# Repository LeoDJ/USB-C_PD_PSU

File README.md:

# USB-C PD PSU
> [!WARNING]
> This is a WIP project. It is not yet recommended to reproduce it in its current state. 

A bidirectional buck-boost DC-DC converter with the following features:
- 240W USB PD EPR (48V 5A)*
- 5-60V input
- 3.3-60V output
- 20A maximum current (theoretically, depending on the thermal solution)
- Constant-current control
- `TI BQ25758A` DC-DC controller
- `WCH CH32X035` as the USB Type-C PD controller (hopefully*)
- Protection of CC and USB data lines up to 63V (`TI TPD4S480`)
- Rough mechanical compatibility with [FranzImsch's parkside-adapter](https://github.com/FranzImsch/parkside-adapter)
- A separate-ish "HMI"/"UI" part of the PCB containing:
  - `XT30` connectors for power in/output
  - 1.47" IPS display
  - Encoder + button controls
  - 1.27mm 2x06 expansion header with a few GPIOs / RS485 for potentially communicating with BMS's, etc.
  - A second `CH32X035`
  - Separable via rotary cutting tool (no mouse bites, because of the high current connections to the XT30 plugs and to not fall into the JLCPCB "two designs" price tier)
- 50x50mm PCB size (50x23mm without the "UI" part)

\* depending on the yet-to-be-written PD firmware (and an actually functioning DC-DC converter layout :P)

You can follow the [Mastodon thread](https://chaos.social/@LeoDJ/113874922536756547) for more up-to-date progress on this project.

&nbsp;

## Hardware
The v1.0 PCB is designed in 8 layers, but 6 would probably suffice too. Thus inner layers 3 and 4 were designed as containing only more GND / power copper pours and can probably be left out, only leading to a reduction of a combined copper thickness from 175µm to 140µm.

### JLCPCB Ordering Settings
- Default, except:
- PCB Thickness: `1.0mm`
- Mark on PCB: `Remove Mark`
- Stencil:
  - (Stencil Side: `Top`)
  - Customized Size: `Yes - 200 x 200mm` (saves on shipping cost)

## References
- ESD-Paw symbol: [diminDDL](https://github.com/diminDDL) ([Source](https://github.com/Caraffa-git/PCB-Art/tree/main/SVG/ESD-paw))
- Paw-shaped Tag-Connect pawprint: [Paw-Connect](https://github.com/LeoDJ/Paw-Connect)

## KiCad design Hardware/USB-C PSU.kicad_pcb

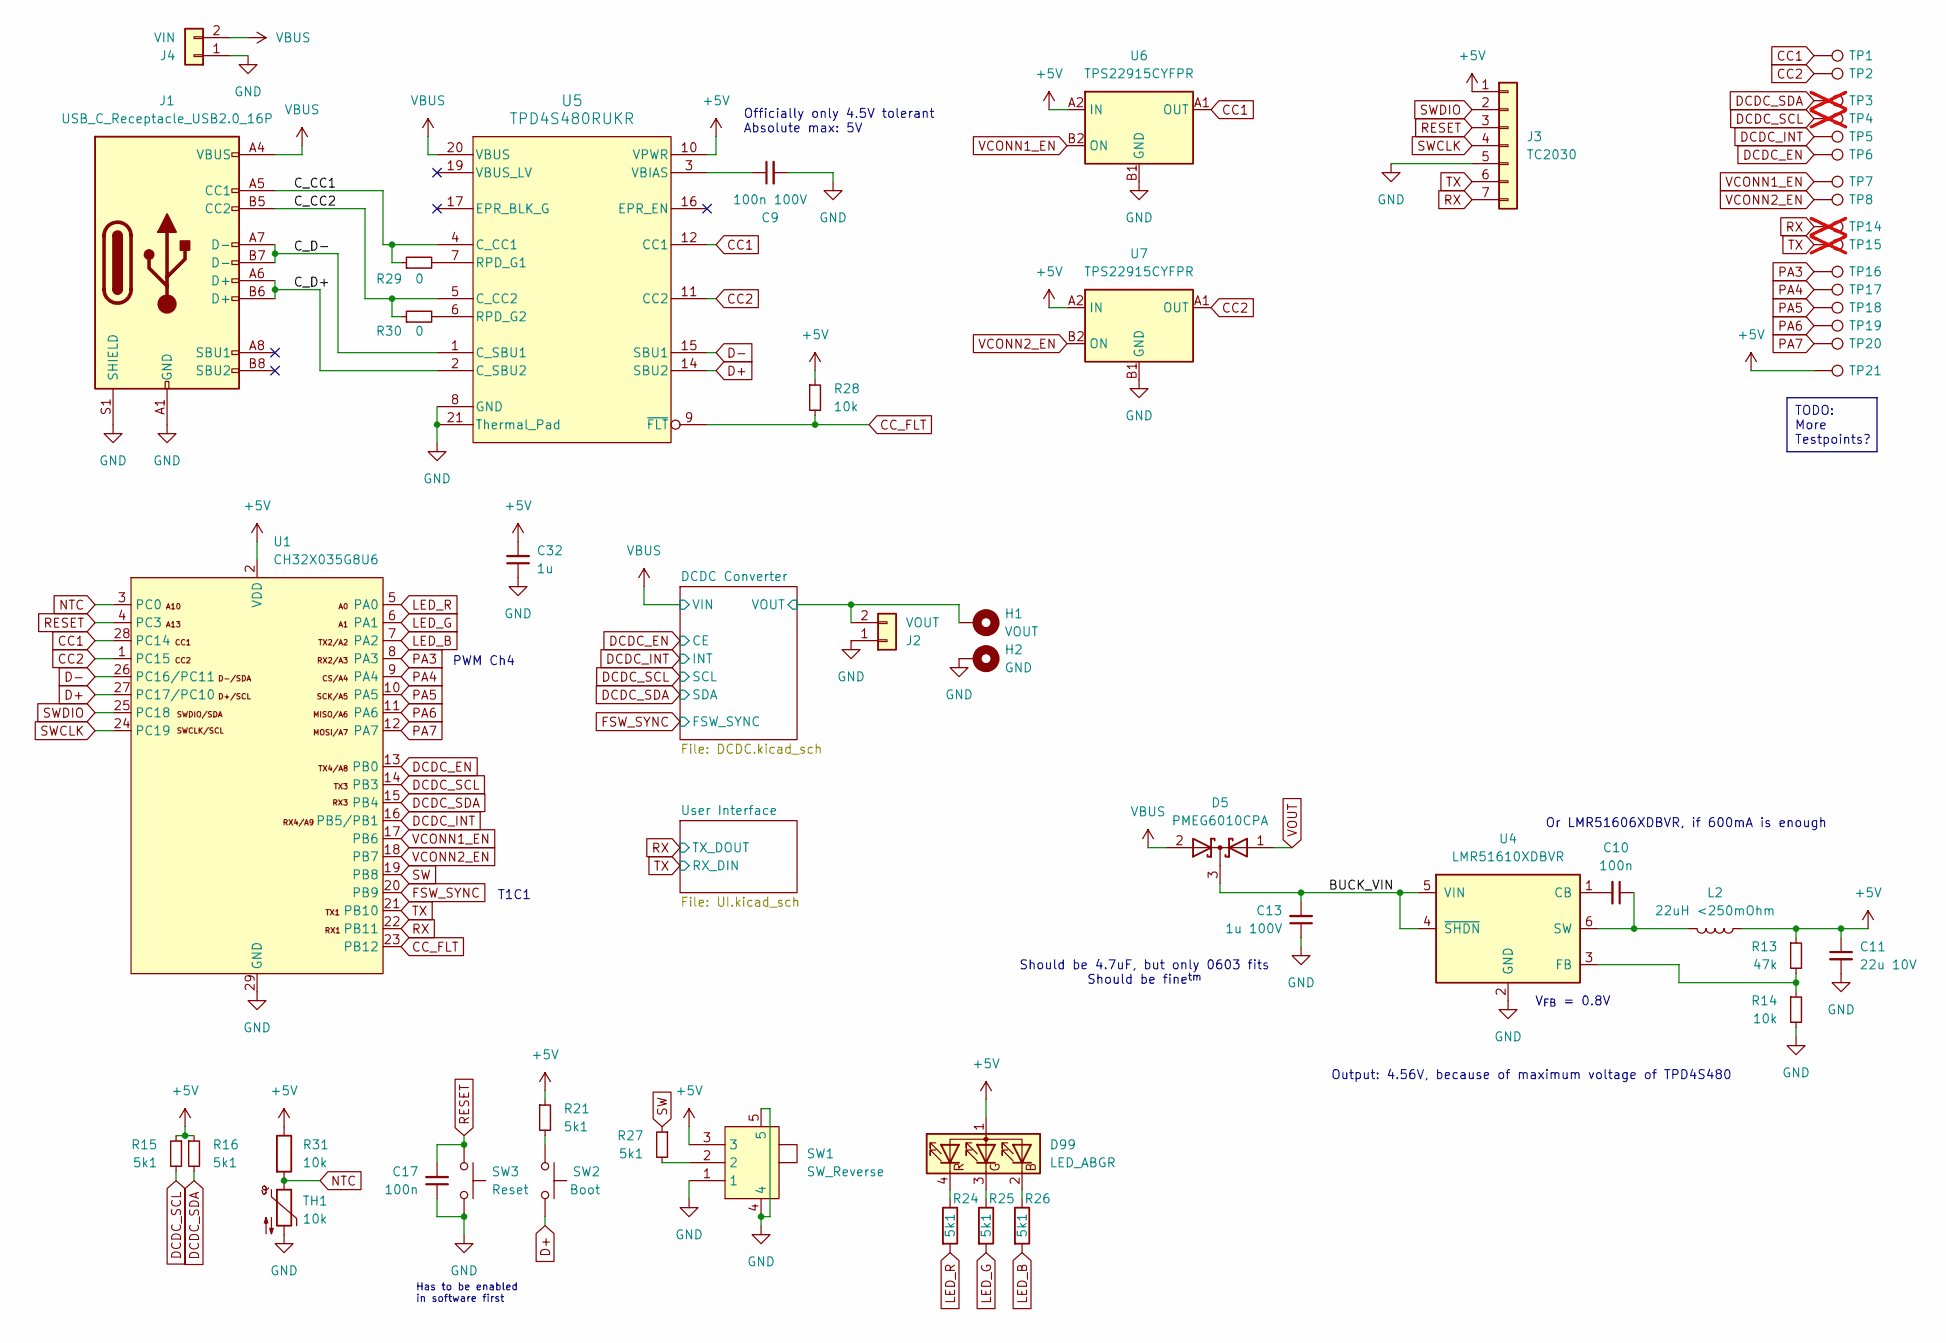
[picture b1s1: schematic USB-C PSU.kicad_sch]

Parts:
C9: 100n 100V; C_0402_1005Metric
C10, C17: 100n; C_0402_1005Metric
C11: 22u 10V; C_0603_1608Metric; LCSC Part C86295
C13: 1u 100V; C_0603_1608Metric
C32: 1u; C_0402_1005Metric
D5: PMEG6010CPA; HUSON-3-1EP_2x2mm_P1.3mm_EP1.1x1.6mm
D99: LED_ABGR; LED-ARRAY-SMD_MHS110FRGBCT; LCSC Part C389528
H1: VOUT; MountingHole_2.2mm_M2_Pad_Via
H2: GND; MountingHole_2.2mm_M2_Pad_Via
J1: USB_C_Receptacle_USB2.0_16P; USB_C_Receptacle_HRO_TYPE-C-31-M-12
J2: VOUT; AMASS_XT30PW-M_1x02_P2.50mm_Horizontal; LCSC Part C431092
J3: TC2030; Paw-Connect_RevB_TC2030-IDC-NL_2x03_P1.27mm_Vertical
J4: VIN; AMASS_XT30PW-M_1x02_P2.50mm_Horizontal; LCSC Part C431092
L2: 22uH <250mOhm; L_Sunlord_MWSA0503S; LCSC Part C718383
R13: 47k; R_0402_1005Metric
R14, R28, R31: 10k; R_0402_1005Metric
R15, R16, R21, R24, R25, R26, R27: 5k1; R_0402_1005Metric
R29, R30: 0; R_0402_1005Metric
SW1: SW_Reverse; SW-SMD_MSK12CO2; LCSC Part C2681570
SW2: Boot; SW-SMD_4P-L3.0-W2.0-P0.85-LS3.5; LCSC Part C256107
SW3: Reset; SW-SMD_4P-L3.0-W2.0-P0.85-LS3.5; LCSC Part C256107
TH1: 10k; R_0402_1005Metric; LCSC Part C77131
TP1, TP2, TP5, TP6, TP7, TP8, TP16, TP17, TP18, TP19, TP20, TP21: TestPoint; TestPoint_Pad_D1.0mm
TP3, TP4, TP14, TP15: TestPoint; TestPoint_Pad_D1.0mm; not fitted
U1: CH32X035G8U6; QFN-28-1EP_4x4mm_P0.4mm_EP2.6x2.6mm; LCSC Part C7437027
U4: LMR51610XDBVR; SOT-23-6; LCSC Part C20539658
U5: TPD4S480RUKR; WQFN-20-1EP_3x3mm_P0.4mm_EP1.7x1.7mm
U6, U7: TPS22915CYFPR; Texas_PicoStar_BGA-4_0.758x0.758mm_Layout2x2_P0.4mm; LCSC Part C1849498

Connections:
+5V: C11.1, C32.2, D99.1 (A), J3.1, L2.2, R13.1, R15.1, R16.1, R21.1, R28.1, R31.1, SW1.3, TP21.1, U1.2 (VDD), U5.10 (VPWR), U6.A2 (IN), U7.A2 (IN); also elsewhere on the board
/BUCK_VIN: C13.2, D5.3 (K), U4.4 (~SHDN), U4.5 (VIN)
/C_CC1: J1.A5 (CC1), R29.1, U5.4 (C_CC1)
/C_CC2: J1.B5 (CC2), R30.1, U5.5 (C_CC2)
/C_D+: J1.A6 (D+), J1.B6 (D+), U5.2 (C_SBU2)
/C_D-: J1.A7 (D-), J1.B7 (D-), U5.1 (C_SBU1)
CC1: TP1.1, U1.28 (PC14), U5.12 (CC1), U6.A1 (OUT)
CC2: TP2.1, U1.1 (PC15), U5.11 (CC2), U7.A1 (OUT)
CC_FLT: R28.2, U1.23 (PB12), U5.9 (~FLT)
D+: SW2.1, U1.27 (PC17/PC10), U5.14 (SBU2)
D-: U1.26 (PC16/PC11), U5.15 (SBU1)
DCDC_EN: TP6.1, U1.13 (PB0); also elsewhere on the board
DCDC_INT: TP5.1, U1.16 (PB5/PB1); also elsewhere on the board
DCDC_SCL: R15.2, TP4.1, U1.14 (PB3); also elsewhere on the board
DCDC_SDA: R16.2, TP3.1, U1.15 (PB4); also elsewhere on the board
FSW_SYNC: U1.20 (PB9); also elsewhere on the board
GND: C9.2, C11.2, C13.1, C17.1, C32.1, H2.1, J1.A1 (GND), J1.A12 (GND), J1.B1 (GND), J1.B12 (GND), J1.S1 (SHIELD), J2.1, J3.5, J4.1, R14.2, SW1.1, SW1.4, SW1.5, SW3.2, TH1.2, U1.29 (GND), U4.2 (GND), U5.8 (GND), U5.13 (GND), U5.18 (GND), U5.21 (Thermal_Pad), U6.B1 (GND), U7.B1 (GND); also elsewhere on the board
LED_B: R26.2, U1.7 (PA2)
LED_G: R25.2, U1.6 (PA1)
LED_R: R24.2, U1.5 (PA0)
NTC: R31.2, TH1.1, U1.3 (PC0)
unnamed: D99.2 (BK), R26.1
unnamed: D99.3 (GK), R25.1
unnamed: D99.4 (RK), R24.1
unnamed: R21.2, SW2.2
unnamed: R27.2, SW1.2
unnamed: C10.2, U4.1 (CB)
unnamed: R13.2, R14.1, U4.3 (FB)
unnamed: C10.1, L2.1, U4.6 (SW)
unnamed: R29.2, U5.7 (RPD_G1)
unnamed: R30.2, U5.6 (RPD_G2)
unnamed: C9.1, U5.3 (VBIAS)
PA3: TP16.1, U1.8 (PA3)
PA4: TP17.1, U1.9 (PA4)
PA5: TP18.1, U1.10 (PA5)
PA6: TP19.1, U1.11 (PA6)
PA7: TP20.1, U1.12 (PA7)
RESET: C17.2, J3.3, SW3.1, U1.4 (PC3)
RX: J3.7, TP14.1, U1.22 (PB11); also elsewhere on the board
SW: R27.1, U1.19 (PB8)
SWCLK: J3.4, U1.24 (PC19)
SWDIO: J3.2, U1.25 (PC18)
TX: J3.6, TP15.1, U1.21 (PB10); also elsewhere on the board
VBUS: D5.2 (A), J1.A4 (VBUS), J1.A9 (VBUS), J1.B4 (VBUS), J1.B9 (VBUS), J4.2, U5.20 (VBUS); also elsewhere on the board
VCONN1_EN: TP7.1, U1.17 (PB6), U6.B2 (ON)
VCONN2_EN: TP8.1, U1.18 (PB7), U7.B2 (ON)
VOUT: D5.1 (A), H1.1, J2.2; also elsewhere on the board

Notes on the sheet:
TODO: More Testpoints?
V_{FB} = 0.8V
PWM Ch4
T1C1
Has to be enabled in software first
Officially only 4.5V tolerant Absolute max: 5V
Should be 4.7uF, but only 0603 fits Should be fine^{tm}
Output: 4.56V, because of maximum voltage of TPD4S480
Or LMR51606XDBVR, if 600mA is enough

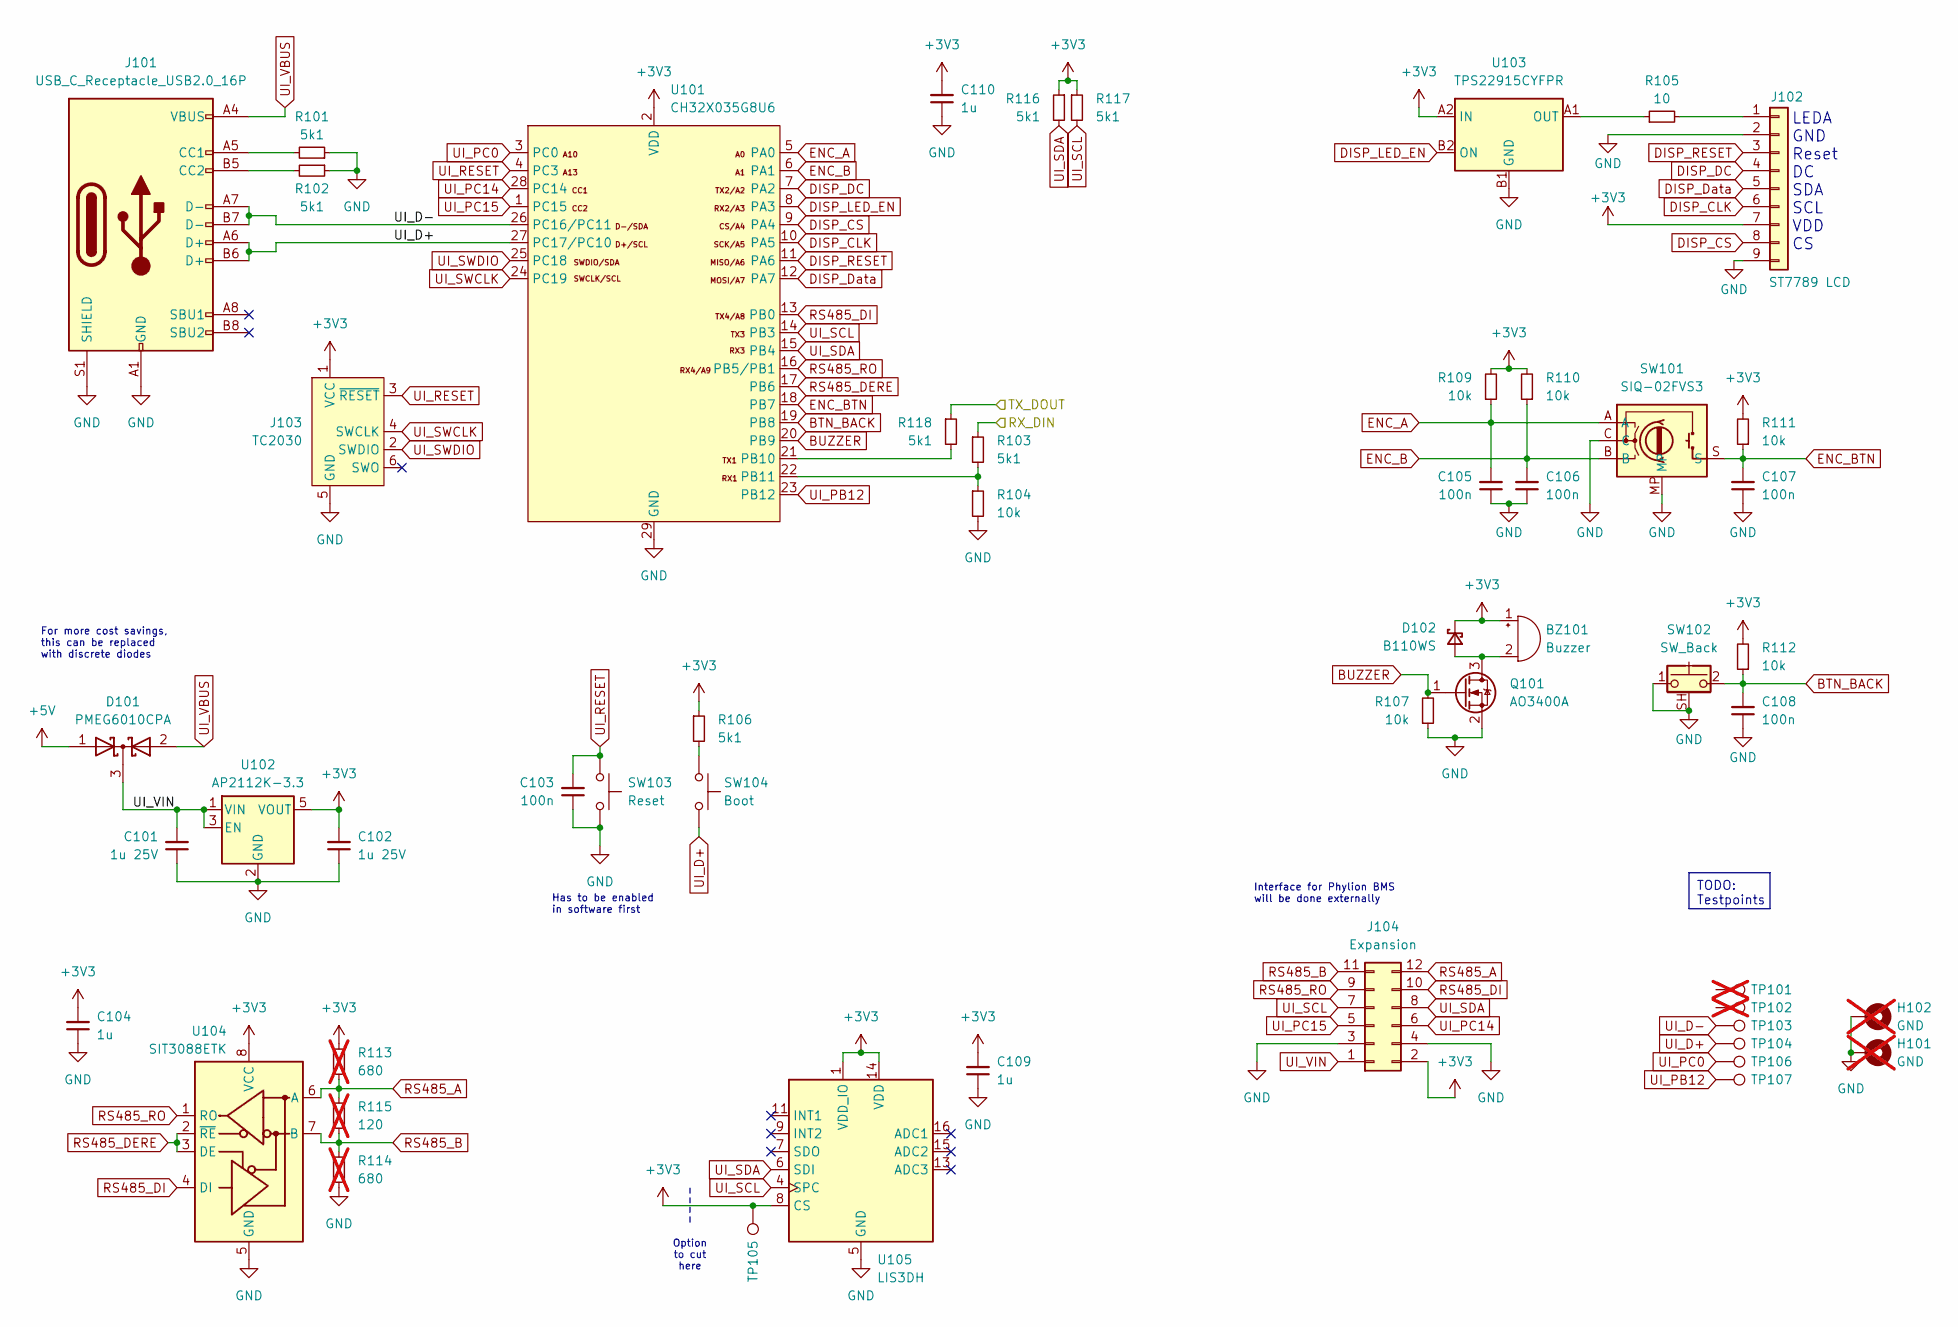
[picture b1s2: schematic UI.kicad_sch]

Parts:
BZ101: Buzzer; BUZ-SMD_L4.0-W4.0-P3.50-L; LCSC Part C391027
C101, C102: 1u 25V; C_0402_1005Metric; LCSC Part C52923
C103, C105, C106, C107, C108: 100n; C_0402_1005Metric
C104, C109, C110: 1u; C_0402_1005Metric
D101: PMEG6010CPA; HUSON-3-1EP_2x2mm_P1.3mm_EP1.1x1.6mm
D102: B110WS; D_SOD-323; LCSC Part C7461125
H101, H102: GND; MountingHole_2.2mm_M2_Pad_Via; not fitted
J101: USB_C_Receptacle_USB2.0_16P; USB_C_Receptacle_HRO_TYPE-C-31-M-12
J102: ST7789 LCD; FPC-SMD_8P-P0.50_HCTL_HC-FPC-05-10-8RLTAG; LCSC Part C5213730
J103: TC2030; Paw-Connect_RevB_TC2030-IDC-NL_2x03_P1.27mm_Vertical
J104: Expansion; PinSocket_2x06_P1.27mm_Horizontal; LCSC Part C2881826
Q101: AO3400A; SOT-23; LCSC Part C347475
R101, R102, R103, R106, R116, R117, R118: 5k1; R_0402_1005Metric
R104, R107, R109, R110, R111, R112: 10k; R_0402_1005Metric
R105: 10; R_0402_1005Metric
R113, R114: 680; R_0402_1005Metric; not fitted
R115: 120; R_0402_1005Metric; not fitted
SW101: SIQ-02FVS3; SW-SMD_SIQ-02FVS3_1; LCSC Part C2925423
SW102: SW_Back; SW-SMD_TS24CA; LCSC Part C393942
SW103: Reset; SW-SMD_4P-L3.0-W2.0-P0.85-LS3.5; LCSC Part C256107
SW104: Boot; SW-SMD_4P-L3.0-W2.0-P0.85-LS3.5; LCSC Part C256107
TP101, TP102: TestPoint; TestPoint_Pad_D1.0mm; not fitted
TP103: D-; TestPoint_Pad_D1.0mm
TP104: D+; TestPoint_Pad_D1.0mm
TP105: TestPoint; TestPoint_Pad_D1.0mm
TP106: PC0; TestPoint_Pad_D1.0mm
TP107: PB12; TestPoint_Pad_D1.0mm
U101: CH32X035G8U6; QFN-28-1EP_4x4mm_P0.4mm_EP2.6x2.6mm; LCSC Part C7437027
U102: AP2112K-3.3; SOT-23-5; LCSC Part C51118
U103: TPS22915CYFPR; Texas_PicoStar_BGA-4_0.758x0.758mm_Layout2x2_P0.4mm; LCSC Part C1849498
U104: SIT3088ETK; DFN-8-1EP_3x3mm_P0.65mm_EP1.55x2.4mm; LCSC Part C601076
U105: LIS3DH; LGA-16_3x3mm_P0.5mm_LayoutBorder3x5y; LCSC Part C15134

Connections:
+3V3: BZ101.1 (+), C102.2, C104.2, C109.2, C110.2, D102.1 (K), J102.7, J103.1 (VCC), J104.2, R106.1, R109.2, R110.2, R111.2, R112.2, R113.2, R116.1, R117.1, TP105.1, U101.2 (VDD), U102.5 (VOUT), U103.A2 (IN), U104.8 (VCC), U105.1 (VDD_IO), U105.8 (CS), U105.14 (VDD)
+5V: D101.1 (A); also elsewhere on the board
BTN_BACK: C108.2, R112.1, SW102.2, U101.19 (PB8)
BUZZER: Q101.1 (G), R107.2, U101.20 (PB9)
DISP_CLK: J102.6, U101.10 (PA5)
DISP_CS: J102.8, U101.9 (PA4)
DISP_DC: J102.4, U101.7 (PA2)
DISP_Data: J102.5, U101.12 (PA7)
DISP_LED_EN: U101.8 (PA3), U103.B2 (ON)
DISP_RESET: J102.3, U101.11 (PA6)
ENC_A: C105.2, R109.1, SW101.A, U101.5 (PA0)
ENC_B: C106.2, R110.1, SW101.B, U101.6 (PA1)
ENC_BTN: C107.2, R111.1, SW101.S, U101.18 (PB7)
GND: C101.1, C102.1, C103.1, C104.1, C105.1, C106.1, C107.1, C108.1, C109.1, C110.1, H101.1, H102.1, J101.A1 (GND), J101.A12 (GND), J101.B1 (GND), J101.B12 (GND), J101.S1 (SHIELD), J102.2, J102.9, J103.5 (GND), J104.3, J104.4, Q101.2 (S), R101.1, R102.1, R104.2, R107.1, R114.1, SW101.C, SW101.MP, SW102.1, SW102.SH (B), SW103.2, U101.29 (GND), U102.2 (GND), U103.B1 (GND), U104.5 (GND), U104.9 (GND), U105.5 (GND), U105.10 (GND), U105.12 (GND); also elsewhere on the board
unnamed: BZ101.2 (-), D102.2 (A), Q101.3 (D)
unnamed: J101.A5 (CC1), R101.2
unnamed: J101.B5 (CC2), R102.2
unnamed: J102.1, R105.2
unnamed: R106.2, SW104.2
unnamed: R118.2, U101.21 (PB10)
unnamed: R103.2, R104.1, U101.22 (PB11)
unnamed: R105.1, U103.A1 (OUT)
RS485_A: J104.12, R113.1, R115.2, U104.6 (A)
RS485_B: J104.11, R114.2, R115.1, U104.7 (B)
RS485_DERE: U101.17 (PB6), U104.2 (~RE), U104.3 (DE)
RS485_DI: J104.10, U101.13 (PB0), U104.4 (DI)
RS485_RO: J104.9, U101.16 (PB5/PB1), U104.1 (RO)
RX: R118.1; also elsewhere on the board
TX: R103.1; also elsewhere on the board
UI_D+: J101.A6 (D+), J101.B6 (D+), SW104.1, TP104.1, U101.27 (PC17/PC10)
UI_D-: J101.A7 (D-), J101.B7 (D-), TP103.1, U101.26 (PC16/PC11)
UI_PB12: TP107.1, U101.23 (PB12)
UI_PC0: TP106.1, U101.3 (PC0)
UI_PC14: J104.6, U101.28 (PC14)
UI_PC15: J104.5, U101.1 (PC15)
UI_RESET: C103.2, J103.3 (~RESET), SW103.1, U101.4 (PC3)
UI_SCL: J104.7, R117.2, U101.14 (PB3), U105.4 (SPC)
UI_SDA: J104.8, R116.2, U101.15 (PB4), U105.6 (SDI)
UI_SWCLK: J103.4 (SWCLK), U101.24 (PC19)
UI_SWDIO: J103.2 (SWDIO), U101.25 (PC18)
UI_VBUS: D101.2 (A), J101.A4 (VBUS), J101.A9 (VBUS), J101.B4 (VBUS), J101.B9 (VBUS)
UI_VIN: C101.2, D101.3 (K), J104.1, U102.1 (VIN), U102.3 (EN)

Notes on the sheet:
TODO: Testpoints
Interface for Phylion BMS will be done externally
Has to be enabled in software first
Option to cut here
LEDA GND Reset DC SDA SCL VDD CS
For more cost savings, this can be replaced with discrete diodes

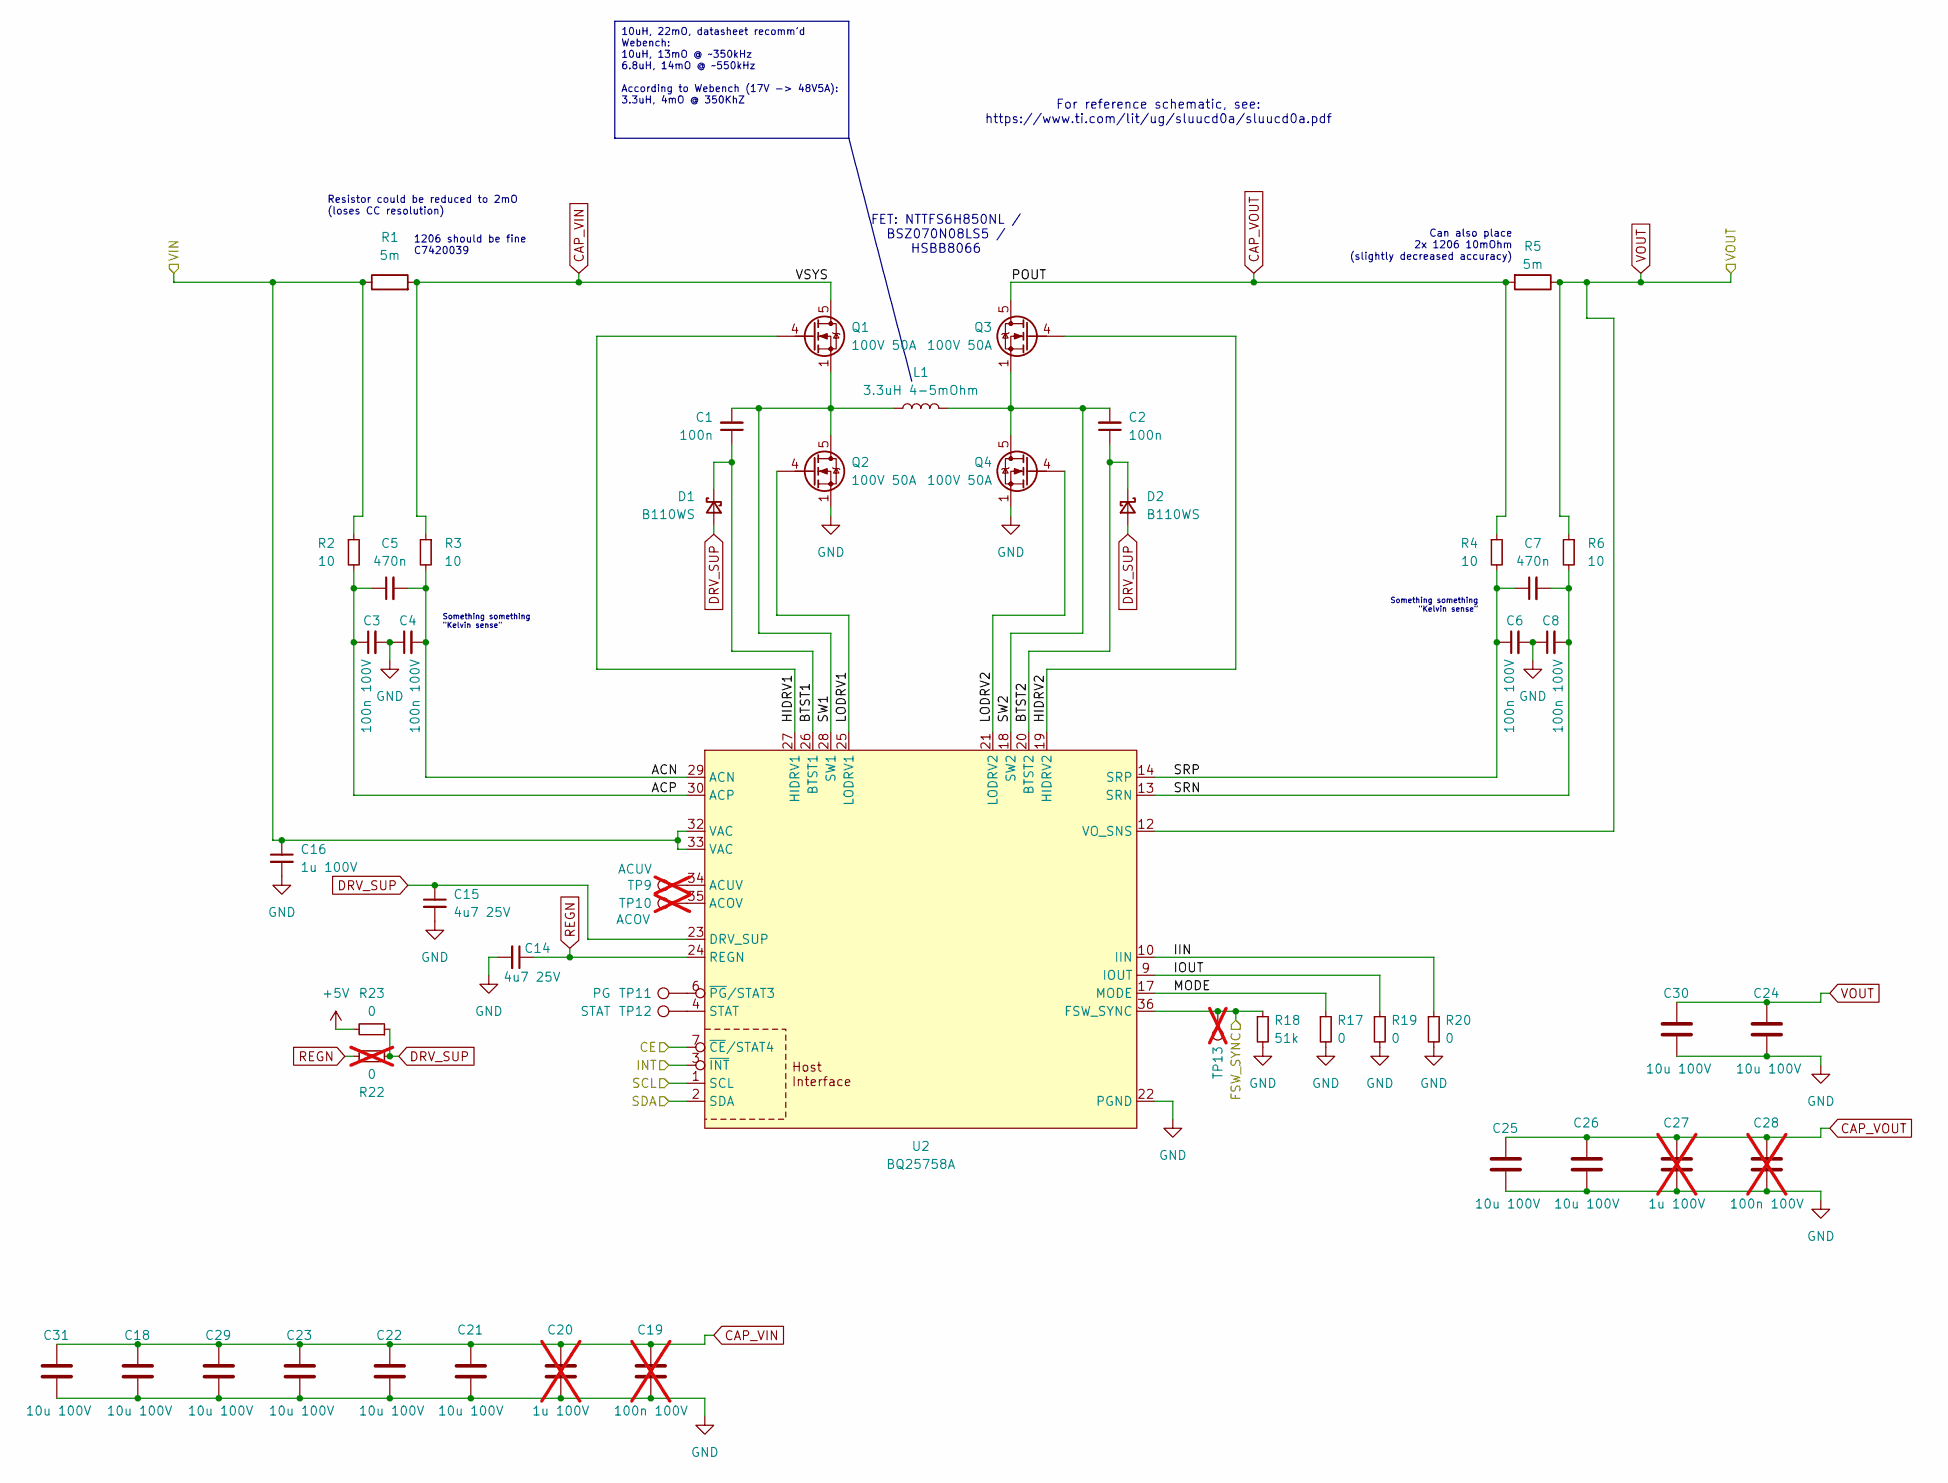
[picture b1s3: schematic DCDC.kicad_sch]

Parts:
C1, C2: 100n; C_0402_1005Metric
C3, C4, C6, C8: 100n 100V; C_0402_1005Metric
C5, C7: 470n; C_0402_1005Metric
C14, C15: 4u7 25V; C_0402_1005Metric
C16: 1u 100V; C_0603_1608Metric
C18, C21, C22, C23, C24, C25, C26, C29, C30, C31: 10u 100V; C_1210_3225Metric; LCSC Part C576517
C19, C28: 100n 100V; C_0402_1005Metric; not fitted
C20, C27: 1u 100V; C_0603_1608Metric; not fitted
D1, D2: B110WS; D_SOD-323; LCSC Part C7461125
L1: 3.3uH 4-5mOhm; L_Chilisin_BMRF00171770; LCSC Part C2976964
Q1, Q2, Q3, Q4: 100V 50A; Diodes_PowerDI3333-8; LCSC Part C534678
R1: 5m; R_1206_3216Metric; LCSC Part C7420039
R2, R3, R4, R6: 10; R_0402_1005Metric
R5: 5m; R_1020_2550Metric_Pad1.33x5.20mm_HandSolder; LCSC Part C843878
R17, R19, R20, R23: 0; R_0402_1005Metric
R18: 51k; R_0402_1005Metric
R22: 0; R_0402_1005Metric; not fitted
TP9: ACUV; TestPoint_Pad_D1.0mm; not fitted
TP10: ACOV; TestPoint_Pad_D1.0mm; not fitted
TP11: PG; TestPoint_Pad_D1.0mm
TP12: STAT; TestPoint_Pad_D1.0mm
TP13: FSW_SYNC; TestPoint_Pad_D1.0mm; not fitted
U2: BQ25758A; Texas_RRV0036A_VQFN-36-1EP_5x6mm_P0.5mm_EP3.6x4.6mm_Thermal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

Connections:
+5V: R23.2; also elsewhere on the board
/DCDC Converter/ACN: C4.2, C5.2, R3.2, U2.29 (ACN)
/DCDC Converter/ACP: C3.1, C5.1, R2.2, U2.30 (ACP)
/DCDC Converter/BTST1: C1.1, D1.1 (K), U2.26 (BTST1)
/DCDC Converter/BTST2: C2.1, D2.1 (K), U2.20 (BTST2)
/DCDC Converter/HIDRV1: Q1.4 (G), U2.27 (HIDRV1)
/DCDC Converter/HIDRV2: Q3.4 (G), U2.19 (HIDRV2)
/DCDC Converter/IIN: R20.1, U2.10 (IIN)
/DCDC Converter/IOUT: R19.1, U2.9 (IOUT)
/DCDC Converter/LODRV1: Q2.4 (G), U2.25 (LODRV1)
/DCDC Converter/LODRV2: Q4.4 (G), U2.21 (LODRV2)
/DCDC Converter/MODE: R17.1, U2.17 (MODE)
/DCDC Converter/SRN: C7.2, C8.2, R6.2, U2.13 (SRN)
/DCDC Converter/SRP: C6.1, C7.1, R4.2, U2.14 (SRP)
/DCDC Converter/SW1: C1.2, L1.1, Q1.1 (S), Q1.2 (S), Q1.3 (S), Q2.5 (D), Q2.6 (D), Q2.7 (D), Q2.8 (D), U2.28 (SW1)
/DCDC Converter/SW2: C2.2, L1.2, Q3.1 (S), Q3.2 (S), Q3.3 (S), Q4.5 (D), Q4.6 (D), Q4.7 (D), Q4.8 (D), U2.18 (SW2)
CAP_VIN: C18.1, C19.1, C20.1, C21.1, C22.1, C23.1, C29.1, C31.1, Q1.5 (D), Q1.6 (D), Q1.7 (D), Q1.8 (D), R1.2, R3.1
CAP_VOUT: C25.1, C26.1, C27.1, C28.1, Q3.5 (D), Q3.6 (D), Q3.7 (D), Q3.8 (D), R4.1, R5.2
DCDC_EN: U2.7 (~CE/STAT4); also elsewhere on the board
DCDC_INT: U2.3 (~INT); also elsewhere on the board
DCDC_SCL: U2.1 (SCL); also elsewhere on the board
DCDC_SDA: U2.2 (SDA); also elsewhere on the board
DRV_SUP: C15.1, D1.2 (A), D2.2 (A), R22.1, R23.1, U2.23 (DRV_SUP)
FSW_SYNC: R18.1, TP13.1, U2.36 (FSW_SYNC); also elsewhere on the board
GND: C3.2, C4.1, C6.2, C8.1, C14.2, C15.2, C16.2, C18.2, C19.2, C20.2, C21.2, C22.2, C23.2, C24.2, C25.2, C26.2, C27.2, C28.2, C29.2, C30.2, C31.2, Q2.1 (S), Q2.2 (S), Q2.3 (S), Q4.1 (S), Q4.2 (S), Q4.3 (S), R17.2, R18.2, R19.2, R20.2, U2.22 (PGND), U2.37 (PAD); also elsewhere on the board
unnamed: TP10.1, U2.35 (ACOV)
unnamed: TP9.1, U2.34 (ACUV)
unnamed: TP12.1, U2.4 (STAT)
unnamed: TP11.1, U2.6 (~PG/STAT3)
REGN: C14.1, R22.2, U2.24 (REGN)
VBUS: C16.1, R1.1, R2.1, U2.32 (VAC), U2.33 (VAC); also elsewhere on the board
VOUT: C24.1, C30.1, R5.1, R6.1, U2.12 (VO_SNS); also elsewhere on the board

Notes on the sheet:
10uH, 22mO, datasheet recomm'd Webench: 10uH, 13mO @ ~350kHz 6.8uH, 14mO @ ~550kHz According to Webench (17V -> 48V5A): 3.3uH, 4mO @ 350KhZ
FET: NTTFS6H850NL / BSZ070N08LS5 / HSBB8066
Something something "Kelvin sense"
1206 should be fine C7420039
Resistor could be reduced to 2mO (loses CC resolution)
Can also place 2x 1206 10mOhm (slightly decreased accuracy)
For reference schematic, see: https://www.ti.com/lit/ug/sluucd0a/sluucd0a.pdf

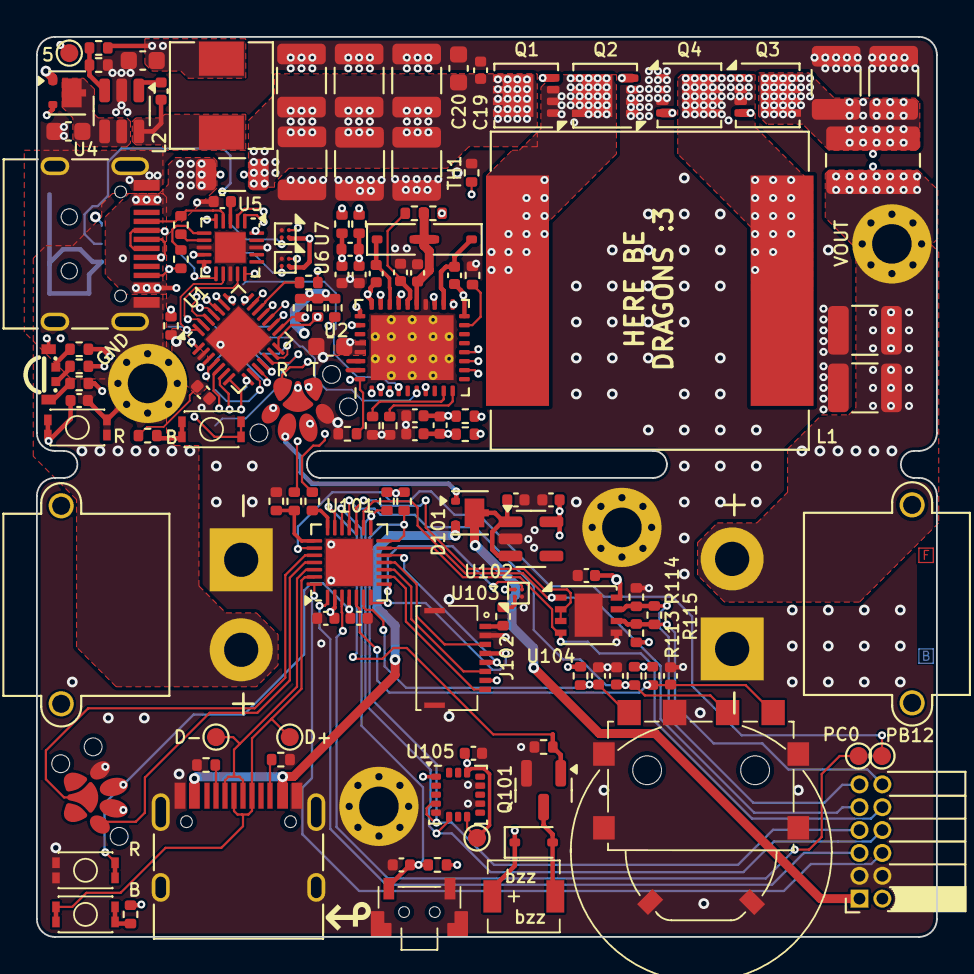
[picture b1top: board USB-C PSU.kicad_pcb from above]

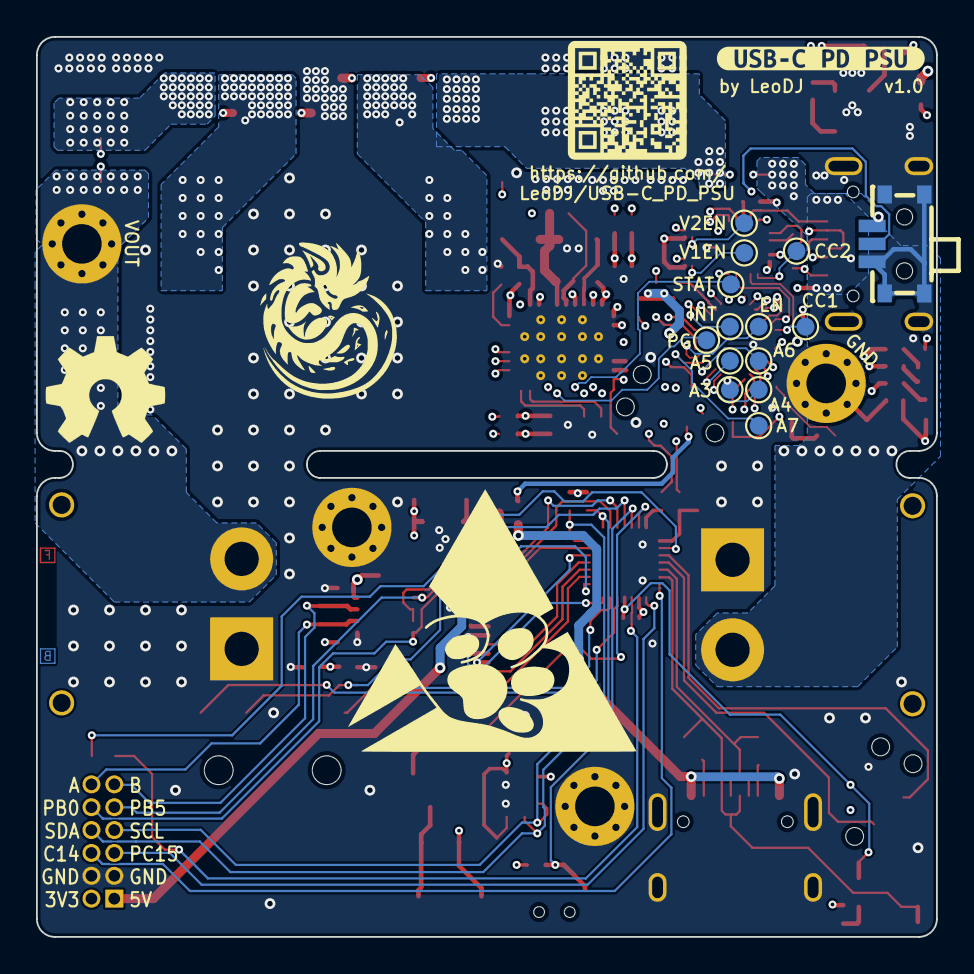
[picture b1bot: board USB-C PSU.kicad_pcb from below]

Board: 8 copper layers, 50.0 x 50.0 mm, 146 parts (15 on the bottom side), 106 nets.

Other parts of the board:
kibuzzard-67A54591: G***; kibuzzard-67A54591

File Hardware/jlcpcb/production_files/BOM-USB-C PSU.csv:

Comment,Designator,Footprint,LCSC
LIS3DH,U105,LGA-16_3x3mm_P0.5mm_LayoutBorder3x5y,C15134
TPS22915CYFPR,"U103,U6,U7",Texas_PicoStar_BGA-4_0.758x0.758mm_Layout2x2_P0.4mm,C1849498
LMR51610XDBVR,U4,SOT-23-6,C20539658
Reset,"SW103,SW104,SW2,SW3",SW-SMD_4P-L3.0-W2.0-P0.85-LS3.5,C256107
SW_Reverse,SW1,SW-SMD_MSK12CO2,C2681570
Expansion,J104,PinSocket_2x06_P1.27mm_Horizontal,C2881826
SIQ-02FVS3,SW101,SW-SMD_SIQ-02FVS3_1,C2925423
3.3uH 4-5mOhm,L1,L_Chilisin_BMRF00171770,C2976964
AO3400A,Q101,SOT-23,C347475
LED_ABGR,D99,LED-ARRAY-SMD_MHS110FRGBCT,C389528
Buzzer,BZ101,BUZ-SMD_L4.0-W4.0-P3.50-L,C391027
SW_Back,SW102,SW-SMD_TS24CA,C393942
VIN,J4,AMASS_XT30PW-M_1x02_P2.50mm_Horizontal,C431092
AP2112K-3.3,U102,SOT-23-5,C51118
ST7789 LCD,J102,FPC-SMD_8P-P0.50_HCTL_HC-FPC-05-10-8RLTAG,C5213730
100V 50A,"Q1,Q2,Q3,Q4",Diodes_PowerDI3333-8,C534678
10u 100V,"C18,C21,C22,C23,C24,C25,C26,C29,C30,C31",C_1210_3225Metric,C576517
SIT3088ETK,U104,DFN-8-1EP_3x3mm_P0.65mm_EP1.55x2.4mm,C601076
22uH <250mOhm,L2,L_Sunlord_MWSA0503S,C718383
5m,R1,R_1206_3216Metric,C7420039
CH32X035G8U6,"U1,U101",QFN-28-1EP_4x4mm_P0.4mm_EP2.6x2.6mm,C7437027
B110WS,"D1,D102,D2",D_SOD-323,C7461125
10k,TH1,R_0402_1005Metric,C77131

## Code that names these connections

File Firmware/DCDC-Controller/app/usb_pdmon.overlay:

#include <dt-bindings/usb-c/pd.h>

/ {

    chosen {
        zephyr,console = &usart1;
    };
/*
    pwmleds {
		compatible = "pwm-leds";
		pwm_ctl: g0 {
			pwms = <&pwm2 0 PWM_USEC(50) PWM_POLARITY_INVERTED>;
			label = "PWM CTL";
		};
	};*/

	
    leds {
        compatible = "gpio-leds";
        led_r:   led_r   { gpios = <&gpioa 0 GPIO_ACTIVE_LOW>;  };
        led_g:   led_g   { gpios = <&gpioa 1 GPIO_ACTIVE_LOW>;  };
        led_b:   led_b   { gpios = <&gpioa 2 GPIO_ACTIVE_LOW>;  };
	};

	aliases {
		usbc-port0 = &port1;
		my-i2c = &gpio_i2c0;
	};

    pwrctrl {
		compatible = "gpio-leds";

		dcdc_en: dcdc_en {
			gpios = <&gpiob 0 GPIO_ACTIVE_LOW>;
			label = "V_CTL2";
		};

		vconn1_en: vconn1_en {
			gpios = <&gpiob 6 GPIO_ACTIVE_HIGH>;
			label = "VCONN1_EN";
		};

		vconn2_en: vconn2_en {
			gpios = <&gpiob 7 GPIO_ACTIVE_HIGH>;
			label = "VCONN2_EN";
		};
	};

	gpio_i2c0: gpio_i2c0 {                                                                                         
		compatible = "gpio-i2c-emod";
		status = "okay";
		clock-frequency = <400000>;
		sda-gpios = <&gpiob 4 GPIO_ACTIVE_HIGH>;
		scl-gpios = <&gpiob 3 GPIO_ACTIVE_HIGH>;
		label = "GPIO_I2C_0";
		#address-cells = <1>;
		#size-cells = <0>;

		bq2575x: charger@6B {
			compatible = "ti,bq2575x";
			reg = <0x6B>;
			status = "okay";
		};
	};


};

&port1 {
	power-role = "source";
	data-role = "dual"; /* actually means disconnected */
	typec-power-opmode = "1.5A";
	source-pdos = <PDO_FIXED(5000, 100, 0) 
		PDO_FIXED(9000, 100, 0) 
		PDO_FIXED(20000, 5000, 0) 
		PDO_FIXED(48000, 100, 0) 
		PDO_PPS_APDO(3300, 48000, 5000)>;
};

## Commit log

2025-02-01 add current state (Schematic done-ish, parts placement done-ish, next up: traces)
2025-02-03 final tweaks before routing traces
2025-02-03 main power layout almost done
    UI board and details still left to do
2025-02-03 UI layout done
2025-02-06 oops, all vias
2025-02-10 design silkscreen markings + some polish
2025-02-13 final tweaks for v1.0
2025-02-14 add documentation
2025-02-16 first display test works
2025-02-26 try creating a zephyr project
    currently borked
2025-03-10 begin BQ25758 implementation
2025-03-10 add BQ25756 register fields
2025-04-04 package BQ2575x as zephyr module
    (it compiles!!)
2025-06-28 [BQ] copy files from zephyr i2c gpio driver
2025-06-28 implement open drain emulation for gpio-i2c
2025-06-28 [BQ] add changes from around april
    (it compiles, but doesn't do very much as of right now)
2025-06-30 [BQ] test: dump I2C registers
2025-07-01 [BQ] basic DCDC control working, it's switching for the first time!
